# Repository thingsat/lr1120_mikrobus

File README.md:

# Semtech LR1120 Mikrobus Board

''The [LR1120](https://fr.semtech.com/products/wireless-rf/lora-edge/lr1120) is an ultra-low power device targeting global geolocation applications. It provides multi band LoRa® and Long Range - Frequency Hopping Spread Spectrum (LR-FHSS) communication over sub-GHz and 2.4GHz Industrial, Scientific and Medical (ISM) bands as well as licensed S-Band for satellites. It integrates a Cloud-native multi-constellation global navigation satellite system (GNSS) scanner and a passive Wi-Fi MAC address scanner, both leveraging [Semtech’s LoRa Cloud™ services](https://www.loracloud.com/documentation/modem_services?url=gls.html#apigeoloclr1110).''

The objective of this student homework is to adapt the [Semtech LR1120 `LR1120MB1DIS` eval board (868 MHz for the SubGhz interface)](https://fr.semtech.com/products/wireless-rf/lora-edge/lr1120dvk1tcks) to the convenient [Mikrobus form factor](https://download.mikroe.com/documents/standards/mikrobus/mikrobus-standard-specification-v200.pdf).

This project is being developed at [Polytech Grenoble](https://www.polytech-grenoble.fr/) and [CSUG](https://www.csug.fr/) ([Université Grenoble-Alpes](https://www.univ-grenoble-alpes.fr/)) by Dante Regiani Freitas and supervised by Prof. Didier Donsez.

## Hardware
* [Schematic](images/schematic.pdf)
* [Kicad design](./kicad)

## Firmware
* [Tutorial on LR11120](https://github.com/CampusIoT/tutorial/tree/master/lr1120)

## Misc
* [TinyGS 2.4 GHz Ground Station](https://github.com/thingsat/tinygs_2g4station)

## Media

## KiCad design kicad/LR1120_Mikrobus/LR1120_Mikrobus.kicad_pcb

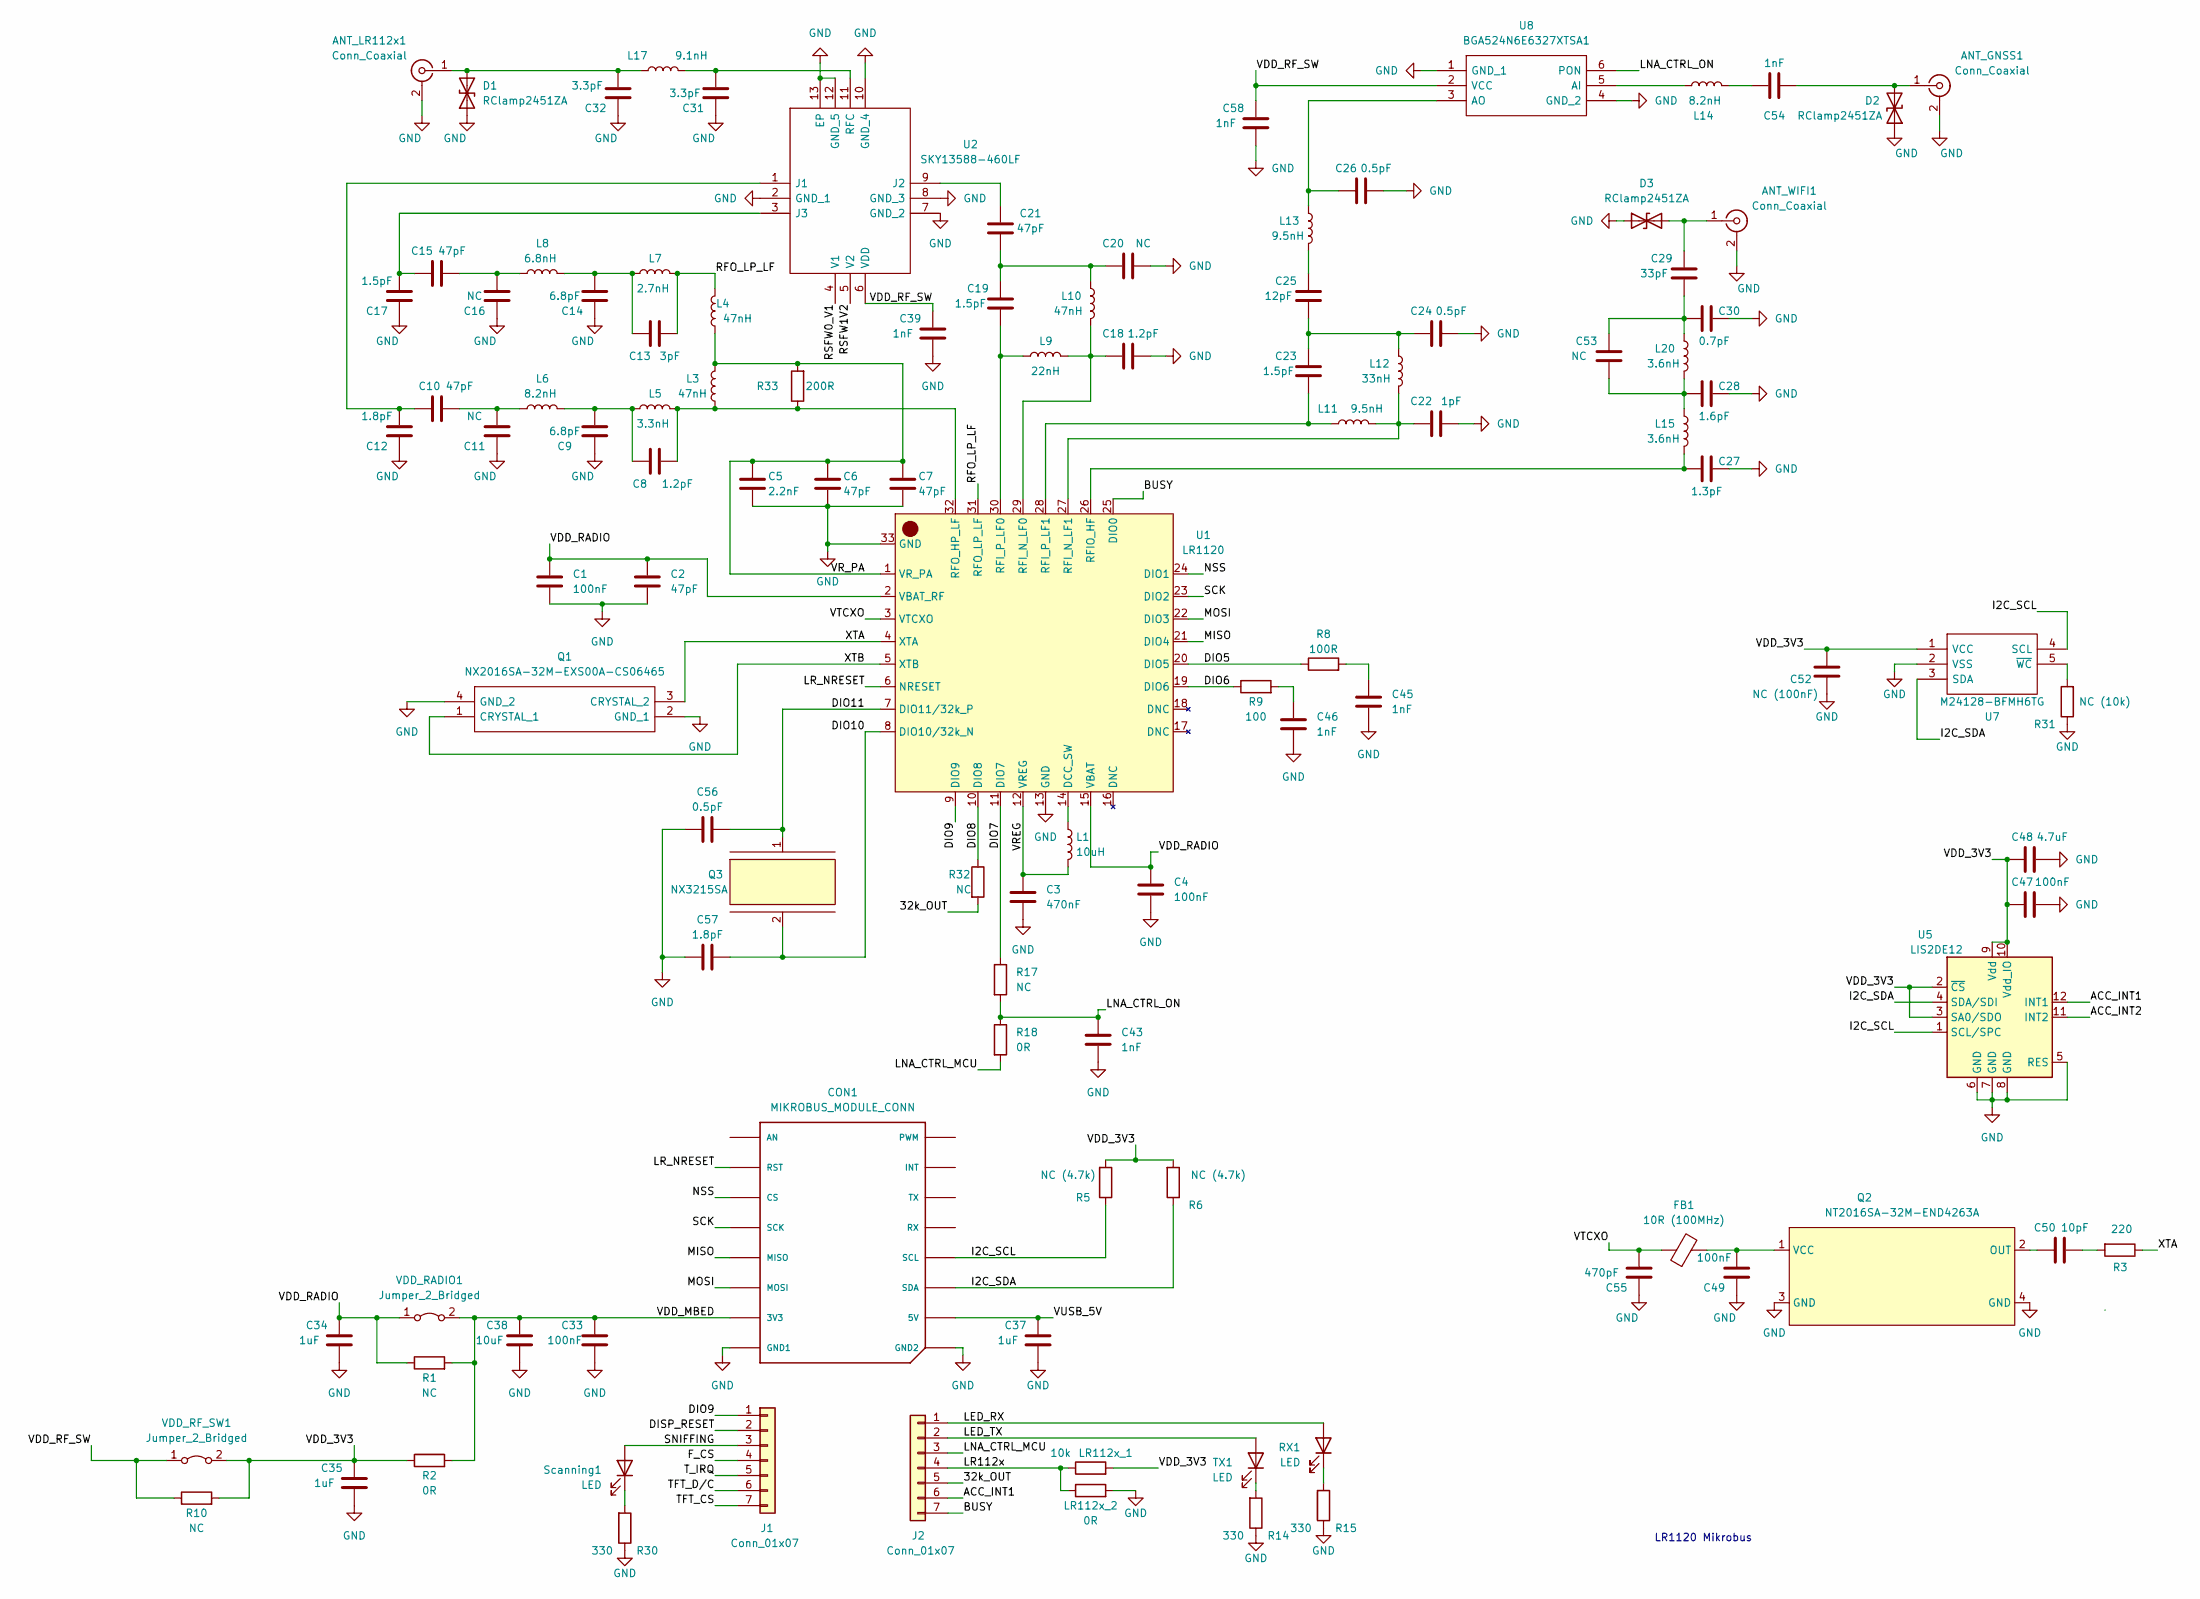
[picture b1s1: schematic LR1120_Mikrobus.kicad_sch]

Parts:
ANT_GNSS1: Conn_Coaxial; U.FL_Hirose_U.FL-R-SMT-1_Vertical
ANT_LR112x1: Conn_Coaxial; U.FL_Hirose_U.FL-R-SMT-1_Vertical
ANT_WIFI1: Conn_Coaxial; U.FL_Hirose_U.FL-R-SMT-1_Vertical
C1, C4, C33, C47, C49: 100nF; C_0201_0603Metric
C2, C6, C7: 47pF; C_0201_0603Metric
C3: 470nF; C_0201_0603Metric
C5: 2.2nF; C_0201_0603Metric
C8, C18: 1.2pF; C_0402_1005Metric
C9, C14: 6.8pF; C_0402_1005Metric
C10, C15, C21: 47pF; C_0402_1005Metric
C11, C16, C20, C53: NC; C_0402_1005Metric
C12: 1.8pF; C_0402_1005Metric
C13: 3pF; C_0402_1005Metric
C17, C19, C23: 1.5pF; C_0402_1005Metric
C22: 1pF; C_0402_1005Metric
C24, C26: 0.5pF; C_0402_1005Metric
C25: 12pF; C_0402_1005Metric
C27: 1.3pF; C_0402_1005Metric
C28: 1.6pF; C_0402_1005Metric
C29: 33pF; C_0402_1005Metric
C30: 0.7pF; C_0402_1005Metric
C31, C32: 3.3pF; C_0402_1005Metric
C34, C35, C37: 1uF; C_0402_1005Metric
C38: 10uF; C_0603_1608Metric
C39, C43, C45, C46, C54, C58: 1nF; C_0201_0603Metric
C48: 4.7uF; C_0402_1005Metric
C50: 10pF; C_0201_0603Metric
C52: NC (100nF); C_0201_0603Metric
C55: 470pF; C_0201_0603Metric
C56: 0.5pF; C_0201_0603Metric
C57: 1.8pF; C_0201_0603Metric
CON1: MIKROBUS_MODULE_CONN
D1, D2, D3: RClamp2451ZA; D_0201_0603Metric
FB1: 10R (100MHz); L_0201_0603Metric
J1, J2: Conn_01x07; PinHeader_1x07_P2.54mm_Vertical
L1: 10uH; L_0603_1608Metric
L3, L4, L10: 47nH; L_0402_1005Metric
L5: 3.3nH; L_0402_1005Metric
L6: 8.2nH; L_0402_1005Metric
L7: 2.7nH; L_0402_1005Metric
L8: 6.8nH; L_0402_1005Metric
L9: 22nH; L_0402_1005Metric
L11, L13: 9.5nH; L_0402_1005Metric
L12: 33nH; L_0402_1005Metric
L14: 8.2nH; L_0201_0603Metric
L15, L20: 3.6nH; L_0402_1005Metric
L17: 9.1nH; L_0402_1005Metric
LR112x_1: 10k; R_0402_1005Metric
LR112x_2: 0R; R_0402_1005Metric
Q1: NX2016SA-32M-EXS00A-CS06465; NX2016SA32MEXS00ACS06465; Mouser Part Number 344-NX2016SA32S06465
Q2: NT2016SA-32M-END4263A
Q3: NX3215SA
R1, R10: NC; R_0603_1608Metric
R2: 0R; R_0603_1608Metric
R3: 220; R_0201_0603Metric
R5, R6: NC (4.7k); R_0201_0603Metric
R8: 100R; R_0201_0603Metric
R9: 100; R_0201_0603Metric
R14, R15, R30: 330; R_0201_0603Metric
R17, R32: NC; R_0201_0603Metric
R18: 0R; R_0201_0603Metric
R31: NC (10k); R_0201_0603Metric
R33: 200R; R_0201_0603Metric
RX1: LED; LED_0402_1005Metric
Scanning1: LED; LED_0402_1005Metric
TX1: LED; LED_0402_1005Metric
U1: LR1120; QFN-32-1EP_5x5mm_P0.5mm_EP3.7x3.7mm_ThermalVias
U2: SKY13588-460LF; QFN50P200X200X65-13N-D; Mouser Part Number 873-SKY13588-460LF
U5: LIS2DE12; LGA-12_2x2mm_P0.5mm
U7: M24128-BFMH6TG; M24128BFMH6TG; Mouser Part Number 511-M24128-BFMH6TG
U8: BGA524N6E6327XTSA1; BGS12SN6E6327XTSA1; Mouser Part Number 726-A524N6E6327XTSA1
VDD_RADIO1: Jumper_2_Bridged; PinHeader_1x02_P2.54mm_Vertical
VDD_RF_SW1: Jumper_2_Bridged; PinHeader_1x02_P2.54mm_Vertical

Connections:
/32k_OUT: J2.5, R32.2
/ACC_INT1: J2.6, U5.12 (INT1)
/ACC_INT2: U5.11 (INT2)
/BUSY: J2.7, U1.25 (DIO0)
/DIO5: R8.1, U1.20 (DIO5)
/DIO6: R9.1, U1.19 (DIO6)
/DIO7: R17.1, U1.11 (DIO7)
/DIO8: R32.1, U1.10 (DIO8)
/DIO9: J1.1, U1.9 (DIO9)
/DIO10: C57.2, Q3.2 (C2), U1.8 (DIO10/32k_N)
/DIO11: C56.2, Q3.1 (C1), U1.7 (DIO11/32k_P)
/DISP_RESET: J1.2
/F_CS: J1.4
/I2C_SCL: CON1.P12 (SCL), R5.1, U5.1 (SCL/SPC), U7.4 (SCL)
/I2C_SDA: CON1.P11 (SDA), R6.1, U5.4 (SDA/SDI), U7.3 (SDA)
/LED_RX: J2.1, RX1.2 (A)
/LED_TX: J2.2, TX1.2 (A)
/LNA_CTRL_MCU: J2.3, R18.2
/LNA_CTRL_ON: C43.1, R17.2, R18.1, U8.6 (PON)
/LR112x: J2.4, LR112x_1.1, LR112x_2.1
/LR_NRESET: CON1.P2 (RST), U1.6 (NRESET)
/MISO: CON1.P5 (MISO), U1.21 (DIO4)
/MOSI: CON1.P6 (MOSI), U1.22 (DIO3)
/NSS: CON1.P3 (CS), U1.24 (DIO1)
/RFO_LP_LF: C13.1, L4.2, L7.2, U1.31 (RFO_LP_LF)
/RSFW0_V1: U2.4 (V1)
/RSFW1V2: U2.5 (V2)
/SCK: CON1.P4 (SCK), U1.23 (DIO2)
/SNIFFING: J1.3, Scanning1.2 (A)
/TFT_CS: J1.7
/TFT_D/C: J1.6
/T_IRQ: J1.5
/VDD_3V3: C35.2, C47.2, C48.2, C52.1, LR112x_1.2, R2.1, R5.2, R6.2, R10.2, U5.2 (~CS), U5.3 (SA0/SDO), U5.9 (Vdd), U5.10 (Vdd_IO), U7.1 (VCC), VDD_RF_SW1.2 (B)
/VDD_MBED: C33.2, C38.2, CON1.P7 (3V3), R1.2, R2.2, VDD_RADIO1.2 (B)
/VDD_RADIO: C1.1, C2.1, C4.1, C34.2, R1.1, U1.2 (VBAT_RF), U1.15 (VBAT), VDD_RADIO1.1 (A)
/VDD_RF_SW: C39.2, C58.2, R10.1, U2.6 (VDD), U8.2 (VCC), VDD_RF_SW1.1 (A)
/VREG: C3.1, L1.2, U1.12 (VREG)
/VR_PA: C5.1, C6.1, C7.1, L3.2, L4.1, R33.2, U1.1 (VR_PA)
/VTCXO: C55.1, FB1.1, U1.3 (VTCXO)
/VUSB_5V: C37.2, CON1.P10 (5V)
/XTA: Q1.3 (CRYSTAL_2), R3.1, U1.4 (XTA)
/XTB: Q1.1 (CRYSTAL_1), U1.5 (XTB)
GND: ANT_GNSS1.2 (Ext), ANT_LR112x1.2 (Ext), ANT_WIFI1.2 (Ext), C1.2, C2.2, C3.2, C4.2, C5.2, C6.2, C7.2, C9.2, C11.2, C12.2, C14.2, C16.2, C17.2, C18.1, C20.1, C22.1, C24.1, C26.1, C27.2, C28.2, C30.2, C31.2, C32.2, C33.1, C34.1, C35.1, C37.1, C38.1, C39.1, C43.2, C45.2, C46.2, C47.1, C48.1, C49.2, C52.2, C55.2, C56.1, C57.1, C58.1, CON1.P8 (GND1), CON1.P9 (GND2), D1.1 (A1), D2.1 (A1), D3.1 (A1), LR112x_2.2, Q1.2 (GND_1), Q1.4 (GND_2), Q2.3 (GND), Q2.4 (GND), R14.1, R15.1, R30.1, R31.1, U1.13 (GND), U1.33 (GND), U2.2 (GND_1), U2.7 (GND_2), U2.8 (GND_3), U2.10 (GND_4), U2.12 (GND_5), U2.13 (EP), U5.5 (RES), U5.6 (GND), U5.7 (GND), U5.8 (GND), U7.2 (VSS), U8.1 (GND_1), U8.4 (GND_2)
unnamed: ANT_GNSS1.1 (In), C54.1, D2.2 (A2)
unnamed: ANT_LR112x1.1 (In), C32.1, D1.2 (A2), L17.1
unnamed: ANT_WIFI1.1 (In), C29.2, D3.2 (A2)
unnamed: C8.1, L3.1, L5.2, R33.1, U1.32 (RFO_HP_LF)
unnamed: C8.2, C9.1, L5.1, L6.2
unnamed: C10.1, C11.1, L6.1
unnamed: C10.2, C12.1, U2.1 (J1)
unnamed: C13.2, C14.1, L7.1, L8.2
unnamed: C15.1, C16.1, L8.1
unnamed: C15.2, C17.1, U2.3 (J3)
unnamed: C18.2, L9.2, L10.2, U1.29 (RFI_N_LF0)
unnamed: C19.1, L9.1, U1.30 (RFI_P_LF0)
unnamed: C19.2, C20.2, C21.1, L10.1
unnamed: C21.2, U2.9 (J2)
unnamed: C22.2, L11.2, L12.2, U1.27 (RFI_N_LF1)
unnamed: C23.1, L11.1, U1.28 (RFI_P_LF1)
unnamed: C23.2, C24.2, C25.1, L12.1
unnamed: C25.2, L13.2
unnamed: C26.2, L13.1, U8.3 (AO)
unnamed: C27.1, L15.2, U1.26 (RFIO_HF)
unnamed: C28.1, C53.1, L15.1, L20.2
unnamed: C29.1, C30.1, C53.2, L20.1
unnamed: C31.1, L17.2, U2.11 (RFC)
unnamed: C45.1, R8.2
unnamed: C46.1, R9.2
unnamed: C49.1, FB1.2, Q2.1 (VCC)
unnamed: C50.1, R3.2
unnamed: C50.2, Q2.2 (OUT)
unnamed: C54.2, L14.2
unnamed: L1.1, U1.14 (DCC_SW)
unnamed: L14.1, U8.5 (AI)
unnamed: R14.2, TX1.1 (K)
unnamed: R15.2, RX1.1 (K)
unnamed: R30.2, Scanning1.1 (K)
unnamed: R31.2, U7.5 (~WC)

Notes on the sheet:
LR1120 Mikrobus

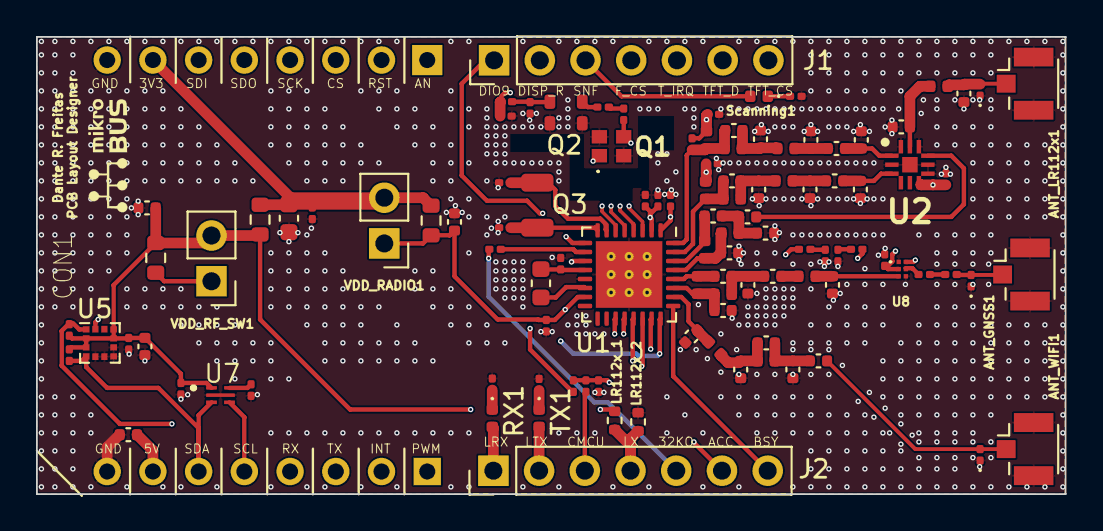
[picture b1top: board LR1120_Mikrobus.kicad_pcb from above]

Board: 4 copper layers, 57.2 x 25.4 mm, 109 parts (0 on the bottom side), 70 nets.

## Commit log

2023-02-02 add contributors
2023-02-02 add dir for external
2023-02-02 add dirs for kicad and firmware
2023-02-02 add todolist
2023-02-02 add kicad project and footprints
2023-02-09 TCXO doc et composant Kicad
    Téléchargement de la documentation du TCXO et création de se composant sur Kicad
2023-02-09 Small corrections from last commit
2023-02-23 tcxo footprint and symbol ready
2023-02-23 Q2 and Q3 placed
    downloaded Q2 symbol and footprint. created Q3 symbol and footprint
2023-03-02 added some res, ind and caps
    added R9, R10, R17, R18 and R32. added C1-C7, C43-C46, C56 and C57. added L1.
2023-03-09 added caps, inds and rclamp
    Added C22-C26, C27-C28, C30, C53 and C58
    Added L11-L13, L15 and L20
    Added D3 (rclamp)
2023-03-16 Added caps, inds and res
    Adeded remaining caps, inds and res, but C47-48, C52 and R31. Some caps, inds and res need be set to the correct footprint and value.
2023-03-26 Added all comp, except connectors
    Added almost all components. Still remains to be placed the microbus connector and the associated caps, res and switches
2023-03-26 Merged files with main
2023-03-27 Here we are changing the value of the capacitors that has conflicts in the table, in the schematics they have 0.5 pF value, but in table is NC
2023-03-27 All changes
2023-03-27 New changes
2023-03-27 Changes: C14 "0.5pF -> 6.8pF
2023-03-27 Resistor R3 modified to 220 ohms, previously not marked in the BOM table.
    TX and RX LED done
    I2C and SPI communication link between LR1120 and Mikrobus done
    3.3 V link done
2023-03-27 All original pins of mikrobus paired. Led's done
2023-03-27 Commit save dante
2023-03-30 Commit finish display
    The connector of mimkrobus were changed with correct names, without changing the standard value like was in the last commit.
    LNA CTRL MCU added to mikrobus
    32k OUT added to mikrobus
    DISP_RESET, T_IRQ, F_CS and TFT_D/C doesn't exist as label in the sheet, they are display labels. This labels were
    created and add to mikrobus.
2023-03-30 created board edges, added ant
    Created board edges, placed antennas
2023-03-30 R13 footprint added
2023-03-30 Capacitor values changed
2023-03-31 all components placed
    all components have been placed. some footprints remain to be properly setup
2023-04-02 all footprints assigned
    All footprints were properly assingned according to the original BOM.
2023-04-03 PCB:populated comp placed connectors
    Populated the PCB with all the components. Placed and locked the connectors
2023-04-03 other components placed
    placed: U2, U8, U1. Q1, Q2 Q3.
2023-04-05 more components placed
2023-04-05 All components placed
    Last step: routing
2023-04-05 all routes traced. ground planes set.
    All routes were traced, The ground planes were set with the appropriate cut out for the crystal oscillators.
2023-04-05 stitched vias. inserted uBUS logo.
2023-04-06 improve readme
2023-04-06 add image
2023-04-06 add dir for images
2023-04-06 add dir for gerber files
2023-04-10 pcb design guideline checked
2023-04-10 gerbers generated
2023-04-10 images added
2023-04-10 update to readme (images)
2023-04-11 create readme for firmware dir
2023-04-11 create license document
2023-04-11 reorg readme
2023-04-11 complete and reorg
2023-04-11 fix images path
2023-04-11 remove lores schematic
2023-04-11 add hires schematic
2023-04-11 add ref to loracloud
2024-03-29 add ref
